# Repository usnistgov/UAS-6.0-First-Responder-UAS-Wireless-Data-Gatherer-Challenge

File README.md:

# [2024 First Responder UAS Wireless Data Gatherer Challenge UAS 6.0](https://www.nist.gov/ctl/pscr/open-innovation-prize-challenges/past-prize-challenges/2024-first-responder-uas-wireless)
**Disclaimer of Non-endorsement**:

Any references to commercial entities, products, services, or other non-governmental
organizations or individuals in this repository are provided solely for the information of
individuals using this document. These references are not intended to reflect the opinion of
NIST, the Department of Commerce or the United States, or its officers or employees. Such
references are not an official or personal endorsement of any product, person, or service, nor
are they intended to imply that the entities, materials, software, or equipment are necessarily the best
available for the purpose. Such references may not be quoted or reproduced for the purpose of
stating or implying an endorsement, recommendation, or approval of any product, person, or
service.

See License tab for licensing information.

> [!NOTE]
> As defined in the software license, this sofware is provided "as-is," meaning that it may not receive future updates and may contain bugs/issues. This repository is provided for reference and archival purposes. Software included in this project may or may not implement "secure" mechanisms, code, configuration, and routines, in partial or whole. Those that do, may be out of date, contain bugs, compromised, not support "best secure practices," and/or contain legacy protocols that contain vulnurabalities.

## Repository Structure
```
Responder UAS Wireless Data Gatherer Challenge UAS 6.0/
├── data_ferry/                     	# Drone Server / Command Server demo code
│   ├── 3D_print_case_models/		   	# 3D Printer case files for Drone Server (To-Do)
│   ├── network_configuration/         	# Configuration and apps to support network functions
│   ├── PKI_configuration/			   	# Apps and support for mTLS and HTTPS
│   ├── server_app/					   	# Drone server Python/Java application
│   ├── server_management/			   	# GUI management and how-to
│   ├── software_installation/		   	# Guide on what software to install on the Raspberry Pi
│   ├── system_install/			       	# Guide on Raspberry Pi OS installation (To-Do)
│   └── README.md
│
├── docs/                              	# Archival documentation from the challenge
│   ├── FN_Connection_process.drawio
│   ├── Network_Schema.drawio
│   ├── UAS_6.0_Official_Rules/
│   ├── UAS_6.0_Stage_2_Guidance/
│   └── UAS_6.0_Stage_3_Guidance/
│
├── foxnode/                           	# FoxNode project (Post Competition)
│   ├── 3D_print_case_models/		   	# 3D Printer case files for FoxNode
│   ├── libraries/					   	# Arduino libraries used in the project
│   ├── pcb_schematic/				   	# PCB Schematics and parts list for FoxNode companion board
│   ├── provision_secrets/				# Supporting PKI Arduino soure code and configuration for FoxNode HTTPS capabilities
│   ├── sample_outputs/					# JSON outputs from FoxNodes
│   ├── stateMachine/					# FoxNode project Arduino source code
│   └── README.md
│
├── pics/                               # Supporting pictures for repository
│
├── stage2_foxnode/                     # Older FoxNode code from Stage 2
│   ├── Foxclient_HTTP/					# Stage 2 FoxNode Arduino source code
│   └── README.md
│
├── stage3_foxnode/                     # Older FoxNode code from Stage 3
│   ├── libraries/						# Arduino libraries to support Stage 3 FoxNode
│   ├── live_event_datasets/			# Collected datasets (JSON) and screenshots from contestant evaluations
│   ├── stateMachine/					# Stage 3 FoxNode project Arduino source code
│   └── README.md
│
├── LICENSE.md							# NIST license and supporting libraries licenses
└── README.md                           # Project overview (this page)
```
## Project Components

- [Data Ferry - PSCR Developed](/data_ferry/README.md)
- [FoxNode Platform - Post Competition](/foxnode/README.md)
- [Stage 2 FoxNode](/stage2_foxnode/README.md)
- [Stage 3 FoxNode](/stage3_foxnode/README.md)

## Terminology
- The sensor device or "FoxNode" is referred to as "sensor", "sensor client", or "IoT-sensor", implied as "ground based" and not airborne.
- The (airborne) drone collecting the data (from the FoxNodes) is referred to as "data ferry", "drone server", or simply "server."
- The device receiving the data from the data ferry is explicitly referred to as the "command server".

Note that conflicts may be present regarding terminology and alignment between the reference code, associated publications, and historical documentation. Above terms will be used interchangeably throughout.

## Scope
This repository contains the reference software for the FoxNode, hardware schematics, 3D-print files, and challenge documentation for the UAS 6.0 Challenge. It also includes post competition, PSCR-developed servers (data ferry and command server) for system testing. The intent of this repository is not only to preserve the software and hardware schematics used in UAS 6.0, but also to serve as a guide for building and replicating the sensor hardware and associated software components used in the competition. Documentation includes UAS 6.0 Official Rules and Guidance documents for Stages 2 and 3. With this information, one could replicate and run the entire UAS 6.0 challenge. Stage 2 and 3 FoxNode code is provided for historical reference and "Post Competition" code is provided that contains additional added enhancements since the compeition conculded.

The "product" of this repository is a ground-based IoT-sensor, based on the Espressif ESP32 System-on-Chip platform that "senses" or generates data, including light levels or lux, temperature, humidity, pressure, accelerometer or motion, associated time stamps, and system-on-chip compute statuses. The system then transmits JSON-formatted data in an HTTP POST message to a predetermined IP address over Wi-Fi. The associated sensor product is extensible to include global positioning system (GPS) data, among other sensors that support the I2C bus. Associated data objects or "placeholders" are present for GPS extensions in the provided code.

A secondary "product" is a Python-based Flask web server for replicating the Data Ferry (Drone Server) and combo Command Server components. Both of these components were required deliverables by challenge participants in Stage 3, but the PSCR lab version is included here for systems-based testing and ongoing development.

## Competition Background
The First Responder Uncrewed Aircraft Systems (UAS) Wireless Data Gatherer Challenge, otherwise known as UAS 6.0, was the sixth competition in the National Institute of Standards and Technology (NIST) Public Safety Communications Research (PSCR) Division’s UAS prize challenge series, which took place between May 2024 and concluded in April of 2025. The challenge evaluated the feasibility and operational value of using UAS as mobile data ferries to support situational awareness in public safety scenarios characterized by sparse, partitioned, or infrastructure-limited communications environments.

Unlike traditional data ferry architectures that rely on delayed, store-and-forward data delivery between disconnected network segments, UAS 6.0 demonstrated how modern commercial UAS platforms, combined with high-power radios, modular payloads, and standardized application interfaces, can enable near real-time data collection and delivery to incident command. During live field evaluations, multiple teams successfully located distributed wireless sensors, [collected environmental data](stage3_foxnode/live_event_datasets/), and delivered actionable information to a command server within minutes, and in some cases, seconds, of acquisition. Results and associated datasets from Stage 3 can be found [here](stage3_foxnode/live_event_datasets/). These capabilities significantly reduced latency compared to legacy data ferry concepts, enabling time-critical decision-making for first responders.

Results from the competition showed that UAS-based data ferries equipped with wide-area communications systems and operator-friendly interfaces provided measurable advantages in coverage, responsiveness, and situational awareness. At the same time, findings highlighted current limitations in autonomous flights, the importance of skilled human operators, and the need for expanded measurement science to evaluate communications performance, interference, and scalability. Collectively, the challenge outcomes will inform future public safety communications research and demonstrate a practical path toward deploying UAS-enabled data ferry systems using commercially available technologies.

## UAS 6.0 Competition Stages
**Stage 1:**  
A proof-of-concept phase that evaluated prototypes based on academic-style paper submissions. In this and subsequent stages, participants followed the rules outlined in the [UAS 6.0 Official Rules](docs/UAS_6.0_Official_Rules.pdf) document, located in the [docs](/docs) section of this repository.

**Stage 2:**  
Stage two took place at participants' home locations, and associated tests were conducted using video assessment methods. The sensor developed in this stage was a minimal viable verification system used for basic message exchange with built-in or "canned" data-generating mechanisms. Details on how this system was implemented and associated tests can be found in the [Guidance for Stage 2](docs/UAS_6.0_Stage_2_Guidance.pdf) document, located in the [docs](/docs) section of this repository. This section is included for historical reference. Anyone looking to replicate or build on elements from UAS 6.0 should start in the [FoxNode Section](foxnode/README.md).

**Stage 3:**  
UAS prize challenge participants competed in-person event to perform NIST-standardized tests and collect data from sensors placed throughout the competition theater. The sensor developed in this stage generated and transmitted environmental data in JSON format from various sensing components. The sensor included a communications state machine to improve data delivery. Details on how this system was implemented and the associated tests can be found in  [Guidance for Stage 3](docs/UAS_6.0_Stage_3_Guidance.pdf) document, located in the [docs](/docs) section of this repository.

# How to Use this Repository

This repository consist of three major parts.  

1. The [Data Ferry](data_ferry/README.md), which is the post-competition, PSCR developed, data ferry that interoperates best with the post-competition FoxNode. This is the best place to start; however, we recommend reviewing the FoxNode requirements and build guide before embarking on this project.
2. The [FoxNode](foxnode/README.md) sensor reference code and associated hardware component support files. This is the post-competition FoxNode that is most compatible with the post-competition Data Ferry.
3. Historical reference code and datasets. One for [Stage 2](/stage2_foxnode/README.md) and one for [Stage 3](/stage3_foxnode/README.md). Developers interested in replicating the UAS 6.0 competition may reference these sections; however, this does not include a functional drone server or associated drone server reference code. Additional documentation for building a drone server can be found in the [docs](docs/) section in [Guidance for Stage 2](docs/UAS_6.0_Stage_2_Guidance.pdf) and [Guidance for Stage 3](docs/UAS_6.0_Stage_3_Guidance.pdf).

# UAS 6.0 Network Architecture

It is important to consider how you plan to deploy the FoxNode sensors and associated servers in your network deployment if you choose to develop on this project.
The following is a greatly simplified architecture that was used in the UAS 6.0 Stage 3 competition. All coded configurations in this repository follow this general schema if you intend to replicate this experiment.

The diagram above shows the three primary components used in UAS 6.0.

- The [Data Ferry](data_ferry/) is the central component configured as a Wi-Fi access point or hotspot. The IP assigned (static provisioning) to the Data Ferry is 192.168.40.20. The mask is 255.255.0.0.

- The [FoxNodes](foxnode/) connect to the Data Ferry when it is in range. FoxNodes are assigned DHCP address (first choice), and failover to "static" IP addresses 192.168.40.80 + FoxNode ID. For example, FoxNode 1 is assigned 192.168.40.81. The mask is 255.255.0.0 or /16. These values are statically set.

> [!NOTE] 
> A 255.255.0.0 mask or /16 "classless" 192.168.0.0 network was chosen for extensiblity in the final stage 3 competition; however, this is not typical, nor practical in most network designs. It is recommended to use a network design that fits your application and architecture. An important factor to consider is how many FoxNodes you plan to deploy, and how many other devices may share the address space. Multi-segment, multi-network, segmentation, and routed architecture is not addressed in this network architecture.

- The Command Server is assigned 192.168.40.10, mask 255.255.0.0. This is statically set. For example, in this repository, this is a simple PC client with web browsing capabilities and can use any non-conflicting address in the /16 address space.

- Internet connectivity is not considered in this architecture to limit scope and to simulate "no" or "limited" connectivity often observed in first responder scenarios, such as wildfires. However, a mobile hotspot or alternative Wi-Fi connection is recommended for development and provisioning purposes.

# Project status
Development status for PSCR - UAS 6.0 First Responder UAS Data Gatherer Challenge
- The UAS 6.0 challenge and associated "works" are considered "complete and finished."
- This repository is for historical reference, and may not receive future updates; however, other PSCR projects may utilize some or all of this project for continued development. 
- Individuals who have questions or are interested in this project or current/future PSCR UAS projects, please contact us at the email address below.

# Recommended To-dos and Implementations
- Deployment package or iso of Data Ferry

- Additional security hardening of Data Ferry
	- Disk encryption (LUKS)
	- Firewall (ufw or iptables)
	- Encrypted secrets in configuration files
	- Disable passwords for SSH and use keys for remote administration
	
- Encrypted secrets on FoxNode NV Ram and associated decryption key in eFuse memory.

- Security audit of Data Ferry and FoxNode code

# Contact
psprizes@nist.gov
- This mailbox is part of a distrubution that is checked regularly.

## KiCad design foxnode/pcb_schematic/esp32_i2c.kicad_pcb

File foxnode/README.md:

# UAS 6.0 Post Competition FoxNode Sensor
The following provides component list and instuction for building and programming the FoxNode sensor.
Note that individuals that intend to replicate the pcb companion board will need to source a pcb fabrication facility and associated board components.
Instruction is not provided on pcb fabrication, but details can be found in [parts list](/foxnode/pcb_schematic/esp32_I2C_Parts_List.csv) and [pcb_schematic](/foxnode/pcb_schematic/)

> [!NOTE]
> PSCR posesses a limited number of "complete" FoxNode sensors. If you wish to develop on this platform or want to borrow our FoxNode sensors for your experimentation, please contact psprizes@nist.gov

> [!NOTE]
> Portions of the FoxNode, Post Competition code was generated with assistance from ChatGPT (OpenAI) and Gemini (Google). The code has been reviewed and integrated by the project authors.

## FoxNode Folder Structure
```
├── foxnode/            	 <-- FoxNode project (Post Competition)
│   ├── 3D_print_case_models <-- gcode, 3mf and dxf files for 3d printing FoxNode cases
│   ├── libraries            <-- Arduino libraries required for Foxnode
│   ├── pcb_schematic        <-- Schematics for FoxNode I2C companion board
│   ├── provision_secrets    <-- FoxNode secrets for NVM storage
│   ├── sample_outputs		 <-- FoxNode JSON outputs
│   ├── stateMachine         <-- FoxNode code (bread and butter of the project)
│   └── README.md            <-- This page
```

## FoxNode Components
**Hardware**: 
- ESP32-S2 ([Adafruit ESP32-S2 TFT Feather](https://learn.adafruit.com/adafruit-esp32-s2-tft-feather/overview))
- Power Bank (optional, but you can use any power bank or source) - [Anker PowerCore Slim 10000 Model A1229](https://www.anker.com/products/a1229) (USB-C out to ESP32)
- USB to USB-C cable (Power source --> ESP32)
- ESP32_I2C Companion Board Schematic [Schematic and Parts List](/foxnode/pcb_schematic/)
- [100mm STEMMA QT / Qwiic JST-SH 4-pin cable](https://www.adafruit.com/product/4210)

**3D-Printed Cases**:
- [3D-Print Case Models](/foxnode/3D_print_case_models/)
- All of the Gcode are sliced for a Prusa MK3s+ printer with a .4mm nozzle and stacked layers at .15 mm (common for most late model 3D printers as of 2026)
- .3mf files are included if you choose to do your own slicing for your specific 3D printer or application
- .gcodes are included for both PLA and PETG filament types, specifically for the Prusa 3D Printer
- Any printer with a .4mm nozzle that uses 1.75mm filament shall work as long as it can accommodate .15mm tall layers
- .dfx CAD files are included for the fabrication of the case window, so the LCD is visible. You will have to source your own fabrication service or device.
- The window should be a .125” thick Lexan or other polycarbonate. The minimum hole size is .125”, so many of the on-line services can create the windows.
- All hardware is 20mm M2.5.  You’ll need 6 per chassis to put the chassis together, and two 8mm to hold in the window on the left side. The M2.5 nylon cap nuts should be used.

> [!NOTE]
> - The ESP32 family of embedded microcontrollers has many different purchasing options that often use different/incompatible displays, bus connections, peripherals, etc. To avoid confusion, it is highly advisable to purchase the specific ESP32 "flavor" mentioned above for the best compatibility with the provided source code. 
> - The I2C Companion Board schematics and [parts list](/foxnode/pcb_schematic/esp32_I2C_Parts_List.csv) are provided in the [pcb_schematic](/foxnode/pcb_schematic/) directory. 

**Software**: 
- Host PC or target to program FoxNode(s), laptop recommended if you are taking it outside
- [Arduino IDE](https://www.arduino.cc/en/software)
- [Arduino Libraries and dependencies](/foxnode/libraries)
- Drone Server. If you need to provision a drone server, please see our build guide [here](/data_ferry/README.md)
- Optional - [KiCad](https://www.kicad.org/) For reading pcb and case CAD files
- Optional - Slicing software for your 3D printer or application, e.g. Bambu Studio, Prusa Slicer

> [!NOTE]
> Up-to-date or current Arduino libraries may also be downloaded via the Arduino IDE libraries interface. For quick deployment and compatibility, the required libaries have been included in this repository, but does not ensure future compatibility, software bug patches, or security patches.

## FoxNode Installation & Setup

### Prerequisites
It is highly recommended to have a functional [data ferry (drone server)](/data_ferry/README.md) before provisioning your FoxNode(s). 

### Step 1: Download repository to local host

Download or clone the UAS 6.0 Github repository to your target "host PC"

```
git clone https://github.com/usnistgov/UAS-6.0-First-Responder-UAS-Wireless-Data-Gatherer-Challenge.git
```

### Step 2: Install Arduino IDE, ESP32 drivers, and project libraries

- Install the [Arduino IDE ](https://www.arduino.cc/en/software) on the target to build project source code and program ESP32 hardware.  

- ESP32 hardware support package dependencies listed below, install via Arduino IDE GUI "[Board Manager](https://docs.arduino.cc/software/ide-v2/tutorials/ide-v2-board-manager/)"   

- Install ExpressIf Software: [esp32](https://github.com/espressif/arduino-esp32) by Espressif Systems -- main "Arduino-esp32" wrapped software stack, search Espressif Systems in the "Boards Manager", select and install.  
	
- Open [stateMachine.ino](/foxnode/stateMachine/stateMachine.ino) file, confirm/acknowlege the creation of "stateMachine" directory.

> [!NOTE]
> Ensure that the project support files "RingBuffer.cpp, httpComms.cpp, etc.", are in the same directory with stateMachine.ino. Typically when you confirm the creation of the directory it will create another directory inside of you current directory. This may incidently create a "nested" directory without the required Arduino C files. You will need to work from the newly created directory because that is where the Arduino IDE expects the files to be.

### Step 3: Move/Copy [libraries](/foxnode/libraries) directory and contents from the cloned repository to the "Arduino" directory in your home directory.

The "libraries" file directory is different from the stateMachine one you created in the previous step. These libraries need to go into the Arduino IDE libraries directory. Alternatively, the libraries can be installed within the Arduino IDE; however, we have included them in this project for compatiblity and time savings. Note that the libraries included here will likely be out of date and not the most current version. Since this is more of an "archival" project, do not expect future updates that support updated libraries.

> [!NOTE]
> The specific path for your cloned GitHub repository and Arduino libraries may differ depending on your system OS and environments. The following commands may be used with modification to match your environment:

Windows: 
```
robocopy "C:\Users\%USERNAME%\Documents\GitHub\UAS-6.0-First-Responder-UAS-Wireless-Data-Gatherer-Challenge\foxnode\libraries" ^
		 "C:\Users\%USERNAME%\Documents\Arduino\libraries" ^
		 /E
```
macOS: 
```
rsync -av \
"$HOME/Documents/GitHub/UAS-6.0-First-Responder-UAS-Wireless-Data-Gatherer-Challenge/foxnode/libraries/" \
"$HOME/Documents/Arduino/libraries/"
```
Linux: 
```
rsync -av \
"$HOME/GitHub/UAS-6.0-First-Responder-UAS-Wireless-Data-Gatherer-Challenge/foxnode/libraries/" \
"$HOME/Arduino/libraries/"
```

## FoxNode Configuration Variables
The FoxNode must be configured for your specific network architecture and it is recommended to change Wi-Fi SSID passwords before proceeding. The network schema can be viewed [here] (/pics/Network_Schema_Example.png). Pre-populated values in this repository are not not secure, are considered compromised, and should not be used.  

IP configuration of the FoxNode follows the following process:  

- FoxNode network configuration is found in the [httpComms.cpp](/foxnode/stateMachine/httpComms.cpp) file and [httpComms.h](/foxnode/stateMachine/httpComms.h) files.

If you are replicating the UAS6 FoxNode architecture, than you do not have to modify these files; however you will have to update the FoxNode ID for each of your FoxNodes.

The FoxNode ID must be unique for each FoxNode and has to be manually configured. The Static FoxNode IP address is formulated using this following function call in [httpComms.h](/foxnode/stateMachine/httpComms.h). This output is for informational purposes:

```
IPAddress getFoxNodeIP(unsigned short thisFoxNodeId){			// Formulate IP address based on Fox-Node ID
	if(thisFoxNodeId >= 175)thisFoxNodeId = 0;				    // This is a safety check to make sure we're not going over 255 when asigning FoxNodes
	return IPAddress(192, 168, 40, thisFoxNodeId + 80);   		// This adds the FoxNode ID plus 80 as the IP address.
```
The FoxNode ID is manually configured in the [eeprrom.cpp](/foxnode/stateMachine/eeprrom.cpp) file.  

### Step 4: Change the FoxNodeId (repeated step for each foxnode)

**THIS VALUE MUST BE CHANGED FOR EACH FOXNODE**
```
void eepromSetVariablesToDefault(void){
	thisFoxNodeId = 10;                  // This is where you manually set the FoxNode ID, Do not assign values greater than 175.
...
}
```
- In the previous example, the FoxNode will be assigned a IP of 192.168.40.90.
- Even if you are using DHCP, this value still needs to be changed to uniquely identify your FoxNodes.

> [!NOTE]
> Do not program your foxnode at this time. You will return to this after PKI configuration in the following steps.

## FoxNode Public Key Infastructure (PKI) Configuration and Wi-Fi Secrets

The FoxNode and Data Ferry (Drone Server) system uses mutual Transport Layer Security (mTLS) for both device authentication and HTTP payload encryption. Before starting this step you will need a Certificate Authority (CA) and a Certificate Server capable of creating client certificates and/or generating Certificate Signing Requests (CSR). If you are using this guide and creating your own drone server, this is covered in the [data ferry PKI Configuration](/data_ferry/PKI_configuration/README.md) section.

### Step 5:

Open and create the "provision_secrets.ino" Arduino project into the Arduino IDE.

Open [provision_secrets.ino](/foxnode/provision_secrets/provision_secrets.ino) file, confirm/acknowlege the creation of "stateMachine" directory.

> [!NOTE]
> As before, ensure that the project support files "secrets.cpp", "secrets.h", and "serial.h" are in the same directory with provision_secrets.ino.

### Step 6: Generate Client FoxNode Certificates

On your signing server (data ferry), create client certificates. A separate certificate is required for each FoxNode in order to uniquely identify them. However, if you are using this in a test environment, you can use a single certificate that all of your FoxNodes use to save time (not recommended), but this defeats per-device identification and authentication.

### Step 7: Copy Privacy Enhanced Mail (PEM) or X.509 information from your drone server

- Generation of the client certificates is cover in [data ferry PKI Configuration](/data_ferry/PKI_configuration/README.md)

You will copy three files from your certificate server to your host PC running Arduino IDE:
- ca/ca.crt - This is the CA certificate
- clients/foxnodeX.crt - This is the FoxNode client certificate
- clients/foxnodeX.key - This is the FoxNode Key

### Step 8: Copy certificate information into provision_secrets.ino

- From Arduino IDE in the provision_secrets.ino project, make sure provision_secrets.ino is selected.  

Scroll down to the first block that shows:
```
-----BEGIN CERTIFICATE-----
```

- The first block should be within a constant varible called "PROV_CA_PEM."  
- Open the "ca.crt" file in a text editor (notepad++, notepad, etc.) and copy everything between "-----BEGIN CERTIFICATE-----" and "-----END CERTIFICATE-----"  
- Go back to Arduino IDE, provision_secrets.ino and paste the certificate information between the "BEGIN" and "END" delimiters.  

- Repeat these steps for "PROV_CLIENT_CERT" using the information in foxnodeX.crt and "PROV_CLIENT_KEY_PEM" using the information in foxnodeX.key.

### Step 9: Modify or update Wi-Fi secrets (if changed)

- Scroll back up to before the first certificate block in provision_secrets.ino.  
- Locate the code section with the WiFi SSIDs and PSKs for both the NTP WiFi and UAS "operational network" networks.
- Confirm or update the SSID and PSK parameters according to your architecture.

### Step 10: Program FoxNode with provision_secrets ino file

In this step you will "upload" the PEM certificate information to the FoxNode's Non-Volatile Memory (NVM) storage. Information stored in this part of memory will persist through reboots and subsequent programming.

- Once everything is copied in and confirmed, connect your PC to the FoxNode USB's port.
- Make sure that your ESP is selected in the COMs port selection dropdown.
- Click the "Upload" arrow button in the top right of the Arduino IDE.

- The "Output" screen should appear in the bottom part of the IDE, and will show the compilation and upload progress. Any compilation errors will appear here.

> [!NOTE]
> The FoxNode LCD may will not show any relevant informaiton at this time.

> [!WARNING]
> While the certificate and secrets are stored in a separate memory space, it is **NOT stored on encrypted media**; meaning, it can be retreaved if the physical device is compromised. For production devices it is recommended to encrypt PEM blocks in NVM and store a read-only decryption key within the ESP32's eFuse memory space. The eFuse memory space can only be written to once and never changed back. This configuration is not covered in this guide, but is recommended for production deployments. See more about eFuses [here](https://docs.espressif.com/projects/esp-idf/en/stable/esp32/api-reference/system/efuse.html)

With the certificate information in place, we can now proceed to programming the FoxNode stateMachine software.

### Step 11: Program the stateMachine software

In step 4, you should have changed the FoxNode's ID to match your current node.  
- Reopen the Arduino IDE project containing the stateMachine project.  
- As before, make sure your FoxNode is selected in the COMs dropdown.  
- Next press the arrow "upload" button to compile and load the stateMachine software.

> [!NOTE]
> This complete's the FoxNode programming portion. If you have additional FoxNodes to program, you will need to repeat steps 4 through 11 for each FoxNode.

# FoxNode Operation and Debugging  

During nominal operation, the FoxNode will operate as follows:

1. The FoxNode sensor will first attempt to auto-connect to the predefined WiFi credentials to obtain NTP clock. In testing, we used a phone with LTE/5G internet access running a Wi-Fi hotspot, using the "UAS_NTP" credentials outlined in the "PROV_NTP_SSID" constant variable in provision_secrets.ino.
2. NTP is optional and the sensor will automatically proceed to the next connection phase if it is unable to connect to an NTP server, but will "freewheel" with incorrect timestamps.
3. Next the FoxNode will attempt to connect to the "production" Wi-Fi network defined in "PROV_UAS6_SSID" within provision_secrets.ino
4. The FoxNode will first request DHCP network configuration from the Drone Server.
5. If the Drone Server does not have a DHCP server configured, the FoxNode will fallback to the hard coded static IP, based on it's FoxNode ID.
6. Once connected the FoxNode will send encrypted HTTPS, HTTP-POST requests to the URI defined in the "UAS_Server" variable the within "httpComms.h" file in the stateMachine Arduino project.
7. FoxNode will continue to send HTTP-POST updates every 10 seconds

- See Appendix B and C of the [UAS_6.0_Stage_3_Guidance](/docs/UAS_6.0_Stage_3_Guidance.pdf) for full FoxNode state machine operation.  
> [!NOTE]
> Stage 3 Guidance does not support DHCP configuration or mTLS, only static addressing and unencrypted HTTP; however the state machine and order of operations remain the same as Stage 3.

> [!NOTE]
> HTTPS mTLS authentication requires that the FoxNode and Drone Server's clock match, therefore it is crutial that NTP sync occur when the FoxNode boots up.

## FoxNode verification

The Arduino IDE provides easy access to a serial interface connection. Setting your serial speed to **230400 baud** displays relevant runtime information. Similar relevant information is also pushed/displayed in a minimal output via an ESP TFT display (unique to the Adafruit ESP32-S2 TFT Feather). From the Arduino IDE, Select Tools > Serial Monitor or Ctrl+Shift+M to display the serial monitor terminal. We have set the baud rate to a higher value of 230400, so not to miss any messages. Ensure that this baud rate is selected in the IDE dropdown in the terminal monitor section.

> [!NOTE]
> Be aware of opening multiple Arduino "projects" and enabling serial monitoring on both instance. If multiple instances are open you may encounter "COM port busy" errors if you try to flash from another instance.

## Logging levels

While debugging messages are implemented throughout the FoxNode code, the ESP32 has limited buffer capabalities for debugging messages. Many debugging "prints" can be suppressed by setting the "serialLogLevel" variable in the [serial.cpp](/foxnode/stateMachine/serial.cpp) stateMachine code to prevent overloading the ESPs processor.  

The function for setting logging levels is located near the top of serial.cpp, along with serial port baud settings, and buffer sizes.
```
// Logging levels are:
//  0 - none      1 - errors   2 - general/high level info   3 - medium info   4 - 4 Very Verbose

void initializeSerial(void){
	serialLogLevel = 1;					// default out of boot is no logging, recommended level 1, 4 may risk overloading MCU
	Serial.begin(230400);			// Start Serial interface
	Serial.setRxBufferSize(2048); // Set buffer bigger for verbose logging
	delay(1000);						// for serial setup
	esp_reset_reason_t r = esp_reset_reason();
	Serial.printf("Reset reason: %d\n", r);
}
```

By default we have set the logging level to level 1, which is the lowest logging level. Logging levels can be adjusted to a more or less verbose output. In our observations, too much logging will often cause the serial monitor function to "freeze" and will no longer display debugging messages until the FoxNode is rebooted. If this occurs, you may have to reduce the logging level.

## Basic Logging Messages

With the FoxNode connected to your target PC, from the Arduino IDE make sure your ESP's COM port is selected in the top dropdown box, then select Tools > Serial Monitor

### A successful FoxNode bootup will go throught the following processes:  

1. FoxNode NTP Connect  
```
Reset reason: 1
**FN-NTP RV-3032 Setup Initiated**
Entering init
Found RV3032
Attempting NTP WiFi Connection to SSID UAS_NTP
.......................................NTP WiFi Connected
FN-NTP Time Set:191351Internet NTP sync OK
```

2. FoxNode INIT, assigns ID set in httpComms.cpp in thisFoxNodeId  
```
**Fox-Node Init**
FoxNode ID: 14
**I2C**
Latched interrupt configured.
setup_webserver_routing() done
```

3. Buffered data queued and sent to Ringbuffer
```
RingBuffer DataPayload Size: 106
Estimated max number of entries possible in Ringbuffer: 1068
```

4. WiFi connected, IP assigned
```
HTTP gate glob_connectedToDrone=1 WiFi.status=3 IP=192.168.41.4
```

5. mTLS configuration loaded and certificate checks
```
mTLS loaded from NVS: YES
CA base64 looks clean
CRT base64 looks clean
KEY base64 looks clean
```

6. First data entry sent and acknowleged
```
Sending 1 Data Entries

MSM case 5 payload bytes=324
```

### Unsucessful NTP Connections

FoxNode will fail to connect to NTP provisioning WiFi, but will fall back to Drone Server.

1. Failed to connect to NTP  
```
Reset reason: 1
**FN-NTP RV-3032 Setup Initiated**
Entering init
Found RV3032
Attempting NTP WiFi Connection to SSID UAS_NTP
............................................................UAS_NTP timeout, switching to Drone Server NTP fallback
```

2. Fall back to drone Server
```
Attempting Drone Server NTP fallback (uas6)...
....uas6 WiFi Connected (fallback)
FN-NTP Time Set:191658Drone Server NTP fallback OK
```

### Uncessful connection to Drone Server

1. Regular boot with NTP provision Server
```
Reset reason: 1
**FN-NTP RV-3032 Setup Initiated**
Entering init
Found RV3032
Attempting NTP WiFi Connection to SSID UAS_NTP
...........NTP WiFi Connected
FN-NTP Time Set:191910Internet NTP sync OK
```

2. FoxNode Initializes and data set to Ring buffer
```
**Fox-Node Init**
FoxNode ID: 14
**I2C**
Latched interrupt configured.
setup_webserver_routing() done
RingBuffer DataPayload Size: 106
Estimated max number of entries possible in Ringbuffer: 1068
```

3. FoxNode will continute to attempt reconnect
```
WiFi disconnected, reason=201
WiFi disconnected, reason=201
WiFi disconnected, reason=201
WiFi disconnected, reason=201
WiFi disconnected, reason=201
WiFi disconnected, reason=201
WiFi disconnected, reason=201
```

This process will continue until a Drone Server is within range.
```
HTTP gate glob_connectedToDrone=1 WiFi.status=3 IP=192.168.40.94
```

FoxNode will complete it's TLS connection and send buffered data.
```
mTLS loaded from NVS: YES
CA base64 looks clean
CRT base64 looks clean
KEY base64 looks clean
WiFi.status=3 IP=192.168.40.94
Target=https://192.168.40.20:8443

Sending 4 Data Entries

MSM case 5 payload bytes=624
Sending 0 Data Entries

MSM case 5 payload bytes=203
```

The FoxNode will retain the self-assigned IP address until either:
a. The Drone Server goes out of range, than back into range (reconnect)
b. The FoxNode is rebooted.

### FoxNode Disconnect
FoxNode disconnects occur because of the following reasons  
a. The Drone Server goes out of range  
b. Weak signal  
c. RF Interference  
d. AP issues on the Drone Server, such as reboot, overload, power issues  
e. FoxNode ESP power instabality, such as low battery, poor or damaged USB or power connector, poor decoupling interface  

The logging error that you will get will be:
```
WiFi disconnected, reason=200
```

### FoxNode Self-Assigns IP and comes into range of Drone server

After about 1 minute, the FoxNode will self-assign an IP based on it's FoxNode ID.
Note that glob_connectedToDrone=0 means it's not connected to a Drone Server
The FoxNode will continute to search for a Drone Server
```
WiFi disconnected, reason=201
WiFi disconnected, reason=201
WiFi disconnected, reason=201
WiFi disconnected, reason=201
WiFi disconnected, reason=201
HTTP gate glob_connectedToDrone=0 WiFi.status=3 IP=192.168.40.94
WiFi disconnected, reason=201
```

Once a Drone Server comes into range it will connect, glob_connectedToDrone=1, means it connected.

## FoxNode Display and Operational States

FoxNode LCD display states.

### NTP Connection at powerup/boot (Yellow)
- Displays FoxNode ID
- NTP connection status
- Timestamp aquired (if connected)
- Subsequnt disconnect

### Not connected to Data Ferry or searching for network (Orange) 
- Timestamp  
- FoxNode ID
- Network search status
- SSID of Drone Server
- SSID PSK Provision status
- IP of Drone Server and secure socket port  

### Connected to Wi-Fi, set IP, handshaking for data exchange (Blue)
- Timestamp
- FoxNode ID
- Wi-Fi Conection state  
- FoxNode IP
- RSSI reading  

### Fully connected to Data Ferry and receiving data (Green)
- Display show Timestamp  
- FoxNode ID
- RSSI reading    
- Foxnode Transmit power (STA_TX_PWR)  
- Drone Server IP and HTTPS socket port (S)  
- Drone Server HTTP Response Code (HTTP Resp)  
- TLS status

## Further Work

The following methods are recommended for further development and device hardening:
- Use eFuse for decryption key and store secrets on NVM encrypted (Recommended)
- Enterprise Wi-Fi (WPA2-Enterprise / WPA3-Enterprise) certificate/device based authentication. This can use the existing certs for mTLS. (Recommended)
- Secure coding audit. Code has not been reviewed for best practices.

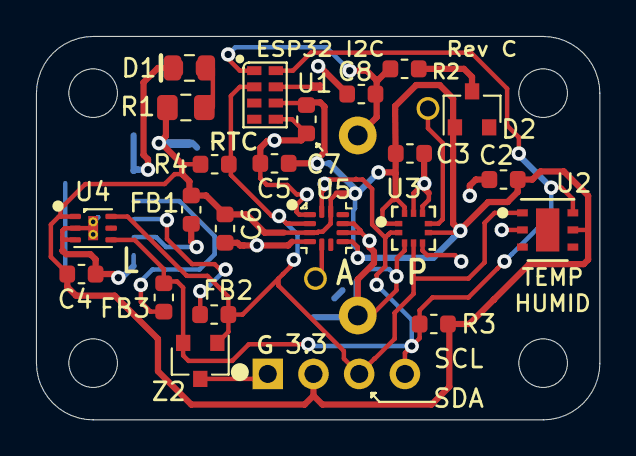
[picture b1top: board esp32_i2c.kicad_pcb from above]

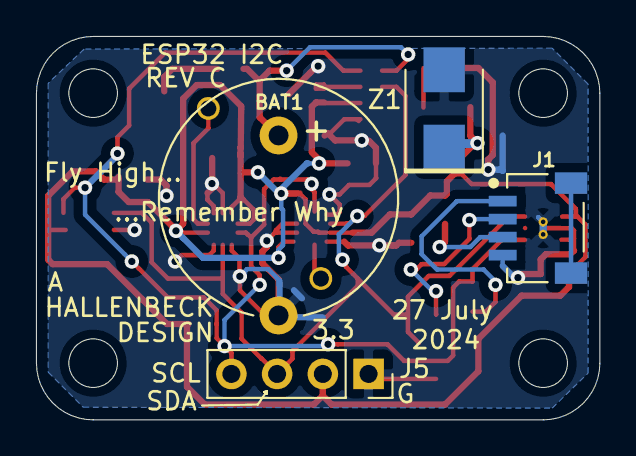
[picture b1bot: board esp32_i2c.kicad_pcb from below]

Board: 2 copper layers, 31.3 x 21.3 mm, 32 parts (4 on the bottom side), 12 nets.

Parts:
BAT1: .33F; Eaton_KR-5R5H334-R
C2, C3, C4, C5, C7, C8: .1uF; R_0603_1608Metric
C6: 1uF; C_0603_1608Metric
D1: LED_Small; 08050603
D2: MMBD7000LT1; SOT-23
FB1, FB2, FB3: Ferrite_Bead_Small; L_0603_1608Metric
H1, H2, H3, H4: MountingHole; MountingHole_2.7mm_M2.5
J1: JST SH 4-Pin; JST-SH-4PIN-HORZ
J3, J4: Conn_01x01; pad50d35
J5: Conn_01x04; PinSocket_1x04_P2.54mm_Vertical
R1: 390; R_0805_2012Metric_Pad1.15x1.40mm_HandSolder
R2: 390; R_0603_1608Metric
R3, R4: 2.74K; R_0603_1608Metric
U1: RV-3032-C7; RV-3032_RTC
U2: Texas-HDC1080; Texas_PWSON-N6
U3: STmicro-LPS22DF; LPS22DFTR
U4: Texas-OPT3001; Texas_USON-N6-DNP0006A-OPT3001
U5: KXTJ3-1057; Bosch_LGA-12_2x2mm_P0.5mm
Z1: 3.3 V; D_SMB
Z2: MMBZ5V6; SOT-23

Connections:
/SCL: FB3.1, J5.4, R3.2, U1.8, U2.6, U3.2, U4.4, U5.12, Z2.2
/SDA: FB2.1, J5.3, R4.2, U1.2, U2.1, U3.4, U4.6, U5.2, Z2.1
/V33: C2.1, C3.1, C4.1, C5.2, C6.1, C7.1, D2.1, FB1.1, J5.2, R1.1, R3.1, R4.1, U1.6, U2.5, U3.1, U3.6, U3.10, U4.1, U5.3, U5.7, U5.11, Z1.1
GND: BAT1.2, C2.2, C3.2, C4.2, C5.1, C6.2, C7.2, C8.2, D1.1, J1.4, J5.1, U1.5, U2.2, U3.3, U3.5, U3.8, U3.9, U4.2, U4.3, U4.7, U4.8, U4.9, U5.1, U5.4, U5.8, U5.9, Z1.2, Z2.3
unnamed: BAT1.1, C8.1, R2.1, U1.1
unnamed: D1.2, R1.2
unnamed: D2.3, R2.2
unnamed: FB1.2, J1.3
unnamed: FB2.2, J1.2
unnamed: FB3.2, J1.1
unnamed: J3.1, U5.5
unnamed: J4.1, U3.7

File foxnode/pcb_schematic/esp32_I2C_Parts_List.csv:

Id,Description,Place or No Place,Designator,Package,Quantity,Designation,Manufacturer,Part Number,Mouser Part Number
1,Coin Cell Supercapacitor,NP,BAT1,Eaton_KR-5R5H334-R,1,.33F,Eaton,KR-5R5H334-R,504-KR-5R5H334-R
2,SMD Resistor,,"C8,C7,C4,C5,C2,C3",R_0603_1608Metric,6,.1uF,"Yageo (or similar, 10% or less)",CC0603KRX7R8BB104,603-CC603KRX7R8BB104
3,Surface Mount Resistor Footprint,NP,R1,R_0805_2012Metric_Pad1.15x1.40mm_HandSolder,1,390,,,
4,Pressure Sensor,,U3,LPS22DFTR,1,STmicro-LPS22DF,ST Micro,LPS22DFTR,511-LPS22DFTR
5,Temperature/Humidity Sensor,,U2,Texas_PWSON-N6  Temp/Humidity,1,Texas-HDC1080,Texas Instraments,HDC1080DMBR,595-HDC1080DMBR
6,Luminosity Sensor,,U4,Texas_USON-N6-DNP0006A-OPT3001   Light,1,Texas-OPT3001,Texas Instraments,OPT3001IDNPRQ1,595-OPT3001IDNPRQ1
7,4-Pin JST SH Connector,NP,J1,JST-SH-4PIN-HORZ,1,JST SH 4-Pin,Adafruit,P4208   (10 pieces in a pack),485-4208
8,Test Point Access Pad,NP,"J4,J3",pad50d35,2,Conn_01x01,"no part, test point access",,
9,Diode,NP,Z1,D_SMB,1,3.3 V,Vishay,SMBJ3V3-E3/52,625-SMBJ3V3-E3
10,Diode,,Z2,SOT-23,1,MMBZ5V6,Diodes Inc,D1213A-02SOL-7,621-D1213A-02SOL-7
11,SMD Resistor,NP,"R3,R4",R_0603_1608Metric,2,2.74K,Any thick-film 1%,,
12,I2C Bus Pin Socket (holes),NP,J5,PinSocket_1x04_P2.54mm_Vertical,1,Conn_01x04,"No part, just holdes",,
13,Accelerometer,,U5,Bosch_LGA-12_2x2mm_P0.5mm Accelerometer,1,KXTJ3-1057,Rohm Semiconductor,KXTJ3-1057,912-KXTJ3-1057
14,Ferrite Bead for EMI Suppression,,"FB1,FB2,FB3",L_0603_1608Metric,3,Ferrite_Bead_Small,Murata,BLM18HE152SN1D,81-BLM18HE152SN1D
15,LED,NP,D1,08050603,1,LED_Small,Any green 0805 or 0603 LED,,
16,Clock,,U1,RV-3032_RTC     Crystal Clock / Real Time Clock,1,RV-3032-C7,Micro Crystal,RV-3032-C7 32.768kHz-2.5PPM-TA-QC,428-203803-MG01
17,Mounting Hole,NP,"H1,H2,H3,H4",MountingHole_2.7mm_M2.5,4,MountingHole,,,
18,SMD Resistor,,C6,C_0603_1608Metric,1,1uF,"Yageo (or similar, 10% or less)",CC0603KRX7R8BB105,603-CC603KRX7R8BB105

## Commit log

2024-08-28 Initial Upload
2024-10-03 Update README.md
    Added non-endorsement disclaimer, 3D Printer model usage, and associated license for the 3D models.
2024-10-03 Added 3D printer models for the ESP case
2024-10-03 Create README_3D_Printer_Models
    Readme for 3D Printer Models
2024-11-18 updated PETG prints, top area window is too tight. added .45mm margin
2025-03-25 First Stage3 Fox-Client source code build passed to the UAS 6.0 prize challegne contestants.
2025-03-25 Updated Stage3 branch to inlucde all nessesary software lib dep's, shown in libraries folder
2025-03-25 Update sensor.cpp
    Updated #include name Ringbuffer.h to RingBuffer.h
2025-04-03 Updated w/ WiFi reconnection fix. updated FN IP assignement range, updated UAS Gateway
2025-04-03 updated RSSI thresh, added a log showing WiFi reconnect
2026-01-21 Update for data ferry , instructions, organization
    Add data ferry and reorganize, update license files, update pics, include more instructions, additional comments to code.
2026-01-21 Update README.md
    markdown rendering updates
2026-01-21 Readme markdown updates
    Readme markdown updates
2026-01-21 Readme formatting corrections
2026-01-21 path updates
2026-01-21 organization updates
    spelling, paths, upload UI photos
2026-01-21 Readme updates
    Additional README updates
2026-01-21 Readme updates
    Tidy up, mostly spacing and formatting corrections
2026-01-21 Update License file
    Spacing and formatting
2026-01-22 Update License.md
    markdown issues
2026-01-23 Mostly comments
    comment fixes and modified IP assignment code on FoxNode
2026-01-23 Update FoxNode for DHCP
    Update for DHCP and increase NTP wait time to 30 seconds
2026-01-28 DHCP updates for FoxNode
    Implement DHCP client on FoxNode with static IP fallback. If FoxNode client can connect to Drone Server WiFi, but does not get DHCP, it will revert to the hard coded IP settings.
2026-01-28 Updated READMEs based on previous FoxNode DHCP updates
    Updated READMEs based on previous FoxNode DHCP updates, added dhcpd.conf and connection process diagram.
2026-02-09 HTTPS/mTLS support added, docs update, add Stage 3 historical code
    Added HTTPS and mutual TLS between the FoxNode and Data Ferry (Drone Server). Updated docs and readme for additions. Added relevant configuration files for Drone Server and source code for FoxNode. M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
2026-02-18 Guide format and spelling fixes, added contestant S3 data
    Guide format and spelling fixes. Fixed some broken links. Added contestant S3 data under FoxNode Stage 3 section.
2026-02-20 Documentation updates
    Updated documentation, added system install section, various formatting changes
2026-03-25 Documentation fixes
2026-03-26 Documentation Updates
2026-04-02 Documentation and configuration file updates
2026-04-14 Formatting updates

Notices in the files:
parts and their libraries:
Copyright 2016 Accelerated Designs. All rights reserved.
